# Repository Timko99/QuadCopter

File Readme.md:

Simple Quadrucopter Project
===========================

> Big Things has small beginnings
> - android David, Prometheus

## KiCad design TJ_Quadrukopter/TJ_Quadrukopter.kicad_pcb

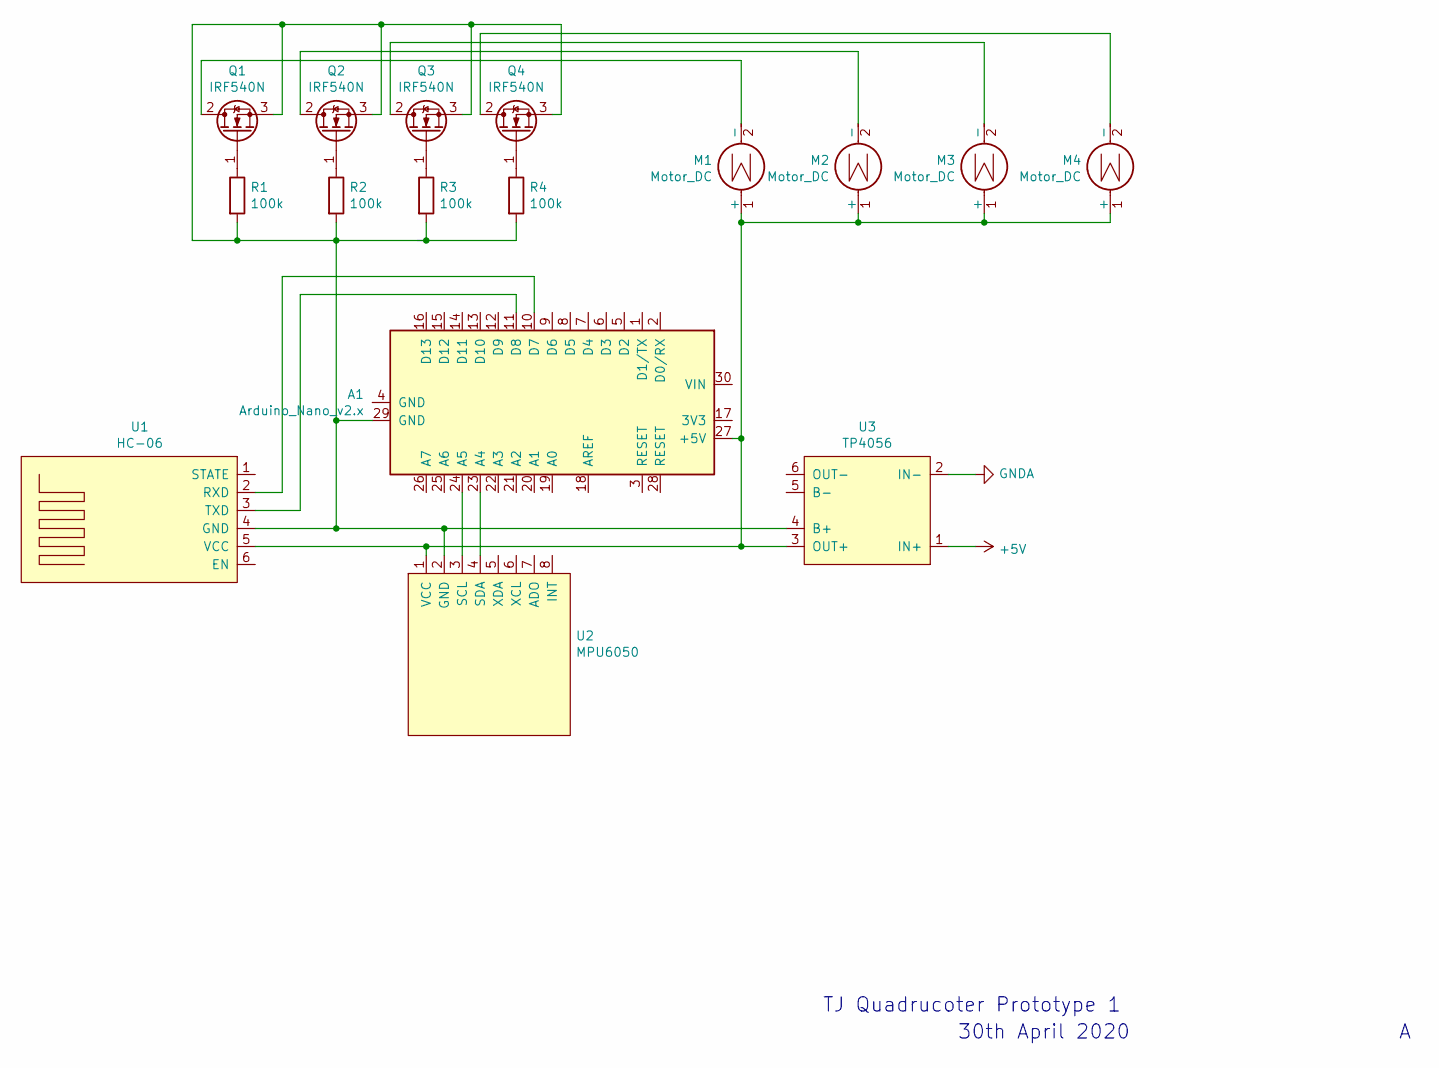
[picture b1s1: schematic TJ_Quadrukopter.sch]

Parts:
A1: Arduino_Nano_v2.x; Arduino_Nano
M1, M2, M3, M4: Motor_DC; PinSocket_1x02_P2.54mm_Vertical
Q1, Q2, Q3, Q4: IRF540N; TO-220-3_Vertical
R1, R2, R3, R4: 100k; R_Axial_DIN0204_L3.6mm_D1.6mm_P5.08mm_Horizontal
U1: HC-06
U2: MPU6050
U3: TP4056

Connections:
+5V: U3.1 (IN+)
GNDA: U3.2 (IN-)
unnamed: A1.10 (D7), U1.2 (RXD)
unnamed: A1.11 (D8), U1.3 (TXD)
unnamed: A1.23 (A4), U2.4 (SDA)
unnamed: A1.24 (A5), U2.3 (SCL)
unnamed: A1.27 (+5V), M1.1 (+), M2.1 (+), M3.1 (+), M4.1 (+), U1.5 (VCC), U2.1 (VCC), U3.3 (OUT+)
unnamed: A1.29 (GND), Q1.3 (S), Q2.3 (S), Q3.3 (S), Q4.3 (S), R1.2, R2.2, R3.2, R4.2, U1.4 (GND), U2.2 (GND), U3.4 (B+)
unnamed: M1.2 (-), Q1.2 (D)
unnamed: M2.2 (-), Q2.2 (D)
unnamed: M3.2 (-), Q3.2 (D)
unnamed: M4.2 (-), Q4.2 (D)
unnamed: Q1.1 (G), R1.1
unnamed: Q2.1 (G), R2.1
unnamed: Q3.1 (G), R3.1
unnamed: Q4.1 (G), R4.1

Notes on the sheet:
TJ Quadrucoter Prototype 1
30th April 2020

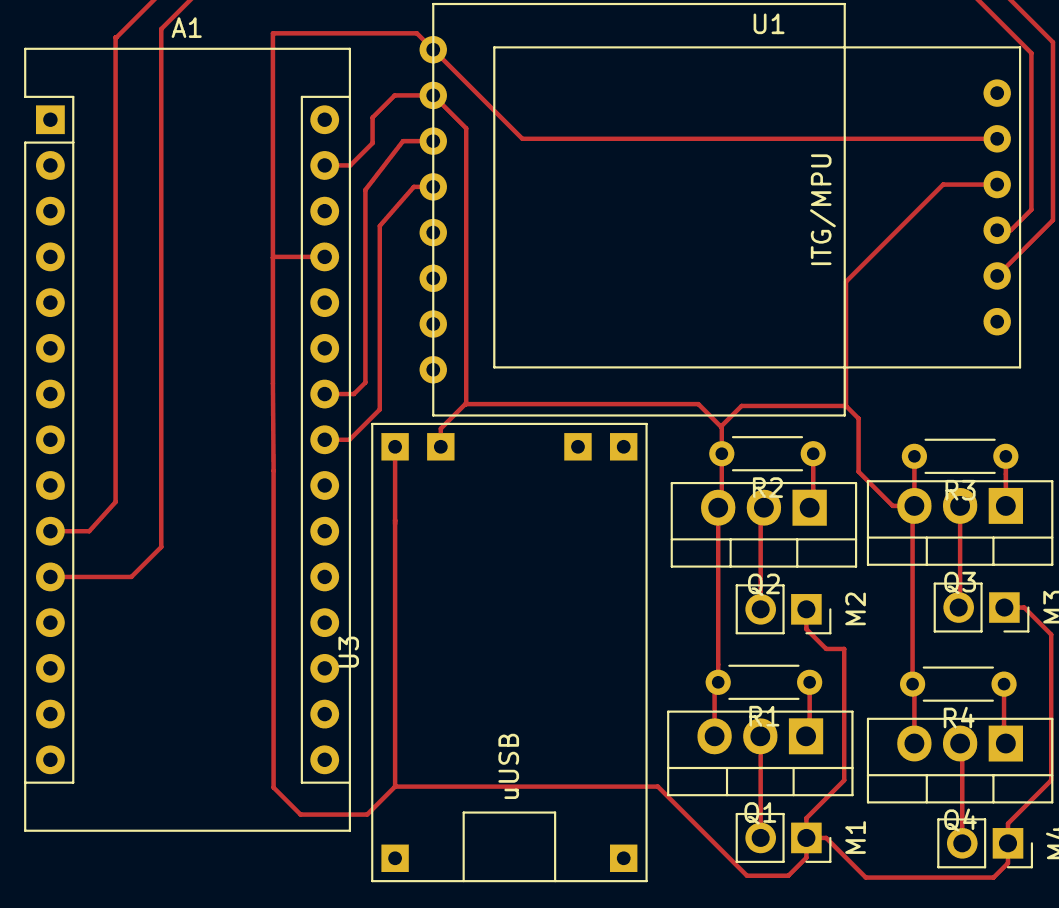
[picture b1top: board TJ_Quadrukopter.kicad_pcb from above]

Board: 2 copper layers, 16 parts (0 on the bottom side), 14 nets.

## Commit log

2020-04-30 Updated Hello World
2020-04-30 Added library for accelerometer&gyroscope module, bluetooth module, power charger module, also added prototype schematic and PCB layout.
    It's still in first phase it was wired under influence of alcohol and in night hours to at least make somethin to doesn't look that I don't care. I provided it as it is, it seems it required rework, 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
2020-05-01 Added original specification from Timko and also mproved board, now it's more compact and its about 5x7cm big.
2020-05-01 Added Readme.md to be cool. Just be cool.
2020-05-01 corrected quote
2020-05-01 Added 3D models for arduino and connect them inside KiCADe, I have placed them before on differen drive path so maybe this will not shown correctly, but all used models and everything is here.
